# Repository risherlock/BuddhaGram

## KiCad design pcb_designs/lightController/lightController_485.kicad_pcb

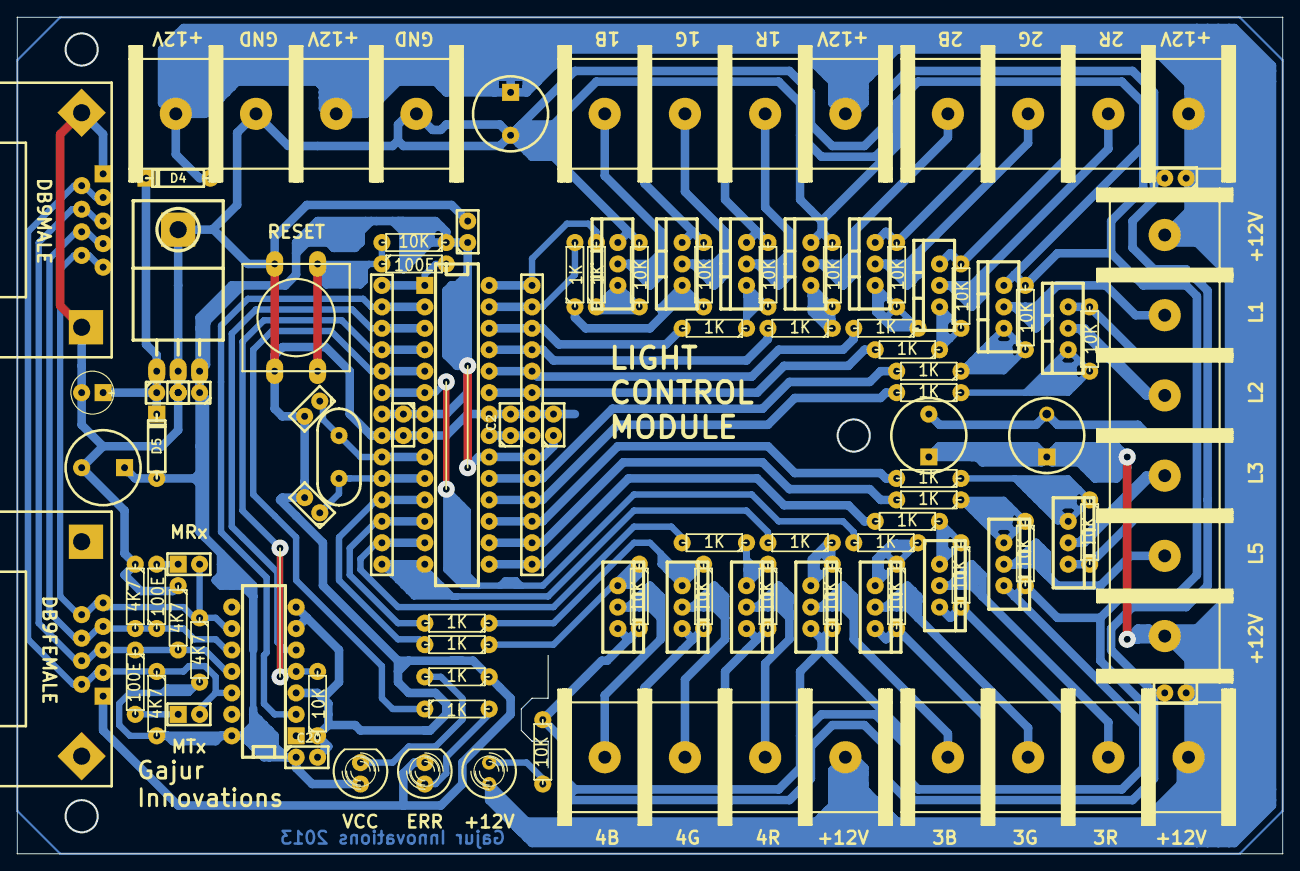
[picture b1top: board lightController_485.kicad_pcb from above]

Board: 2 copper layers, 149.9 x 99.1 mm, 98 parts (0 on the bottom side), 70 nets.

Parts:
C1, C3: 22pF; C1
C2, C5, C12, C13, C14, C15, C16, C20, C21: 104; C1
C4, C7, C8, C9: 1000uF; C2V8
C6: 1000uF; C1V5
D1, D2, D3: LED; LED-5MM
D4, D5: DIODE; D3
IC1: ATMEGA168-P; DIP-28__300
J1: DB9M; DB9MC
J2: DB9F; DB9FC
JP1, JP2: JUMPER; SIL-2
P1, P2: CONN_14; SIL-14
P3, P4, P5, P6, P7: CONN_4; CONN_4_SOLAR
P8: CONN_6; CONN_6_SOLAR
Q1, Q2, Q3, Q4, Q5, Q6, Q7, Q8, Q9, Q10, Q11, Q12, Q13, Q14, Q15, Q16: TIP122; TO-220_Neutral123_Vertical
R1, R4, R6, R7, R8, R9, R10, R11, R12, R13, R14, R15, R16, R17, R18, R19, R20, R21: 1K; R3
R2, R5, R22, R23, R24, R25, R26, R27, R28, R29, R30, R31, R32, R33, R34, R35, R36, R37, R38: 10K; R3
R3, R40, R43: 100E; R3
R39, R41, R42, R44: 4K7; R3
SW1: SW_PUSH; SW_PUSH-12mm
U1: 7805; TO-220_Neutral123_Horizontal
U2: MAX13080E; DIP-14__300
X1: 16MHz; HC-49V

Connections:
+12V: C7.1, C8.1, C9.1, C12.1, C13.1, D3.1, D4.1, P3.2, P3.4, P4.1, P5.1, P6.1, P7.1, P8.1, P8.6
/MISO: IC1.18, P2.4, R12.2
/MOSI: IC1.17, P2.3, R21.2
/P1: IC1.1, P1.1, R3.2
/P2: IC1.2, P1.2, U2.2
/P3: IC1.3, P1.3, U2.5
/P4: IC1.4, P1.4, R22.2, U2.4
/P5: IC1.5, P1.5, R1.1
/P6: IC1.6, P1.6, R18.2
/P9: C1.1, IC1.9, P1.9, X1.1
/P10: C3.1, IC1.10, P1.10, X1.2
/P11: IC1.11, P1.11, R16.2
/P12: IC1.12, P1.12, R15.2
/P13: IC1.13, P1.13, R14.2
/P14: IC1.14, P1.14, R19.2
/P15: IC1.15, P2.1, R17.2
/P16: IC1.16, P2.2, R20.2
/P19: IC1.19, P2.5, R13.2
/P21: C2.1, IC1.21, P2.7
/P23: IC1.23, P2.9, R9.2
/P24: IC1.24, P2.10, R10.2
/P25: IC1.25, P2.11, R11.2
/P26: IC1.26, P2.12, R6.2
/P27: IC1.27, P2.13, R7.2
/P28: IC1.28, P2.14, R8.2
/R0: J1.4, J1.8, J2.4, J2.8, R40.1, R41.2, U2.10
/R1: J1.5, J1.9, J2.5, J2.9, JP1.2, R39.1, U2.9
/RST_IN: R2.2, R3.1, SW1.2
/T0: J1.3, J1.7, J2.3, J2.7, R43.1, R44.2, U2.11
/T1: J1.2, J1.6, J2.2, J2.6, JP2.2, R42.1, U2.12
GND: C1.2, C2.2, C3.2, C4.2, C5.2, C6.2, C7.2, C8.2, C9.2, C12.2, C13.2, C14.2, C15.2, C16.2, C20.2, C21.2, D1.2, IC1.8, IC1.22, J1.1, J2.1, P1.8, P2.8, P3.1, P3.3, Q1.3, Q2.3, Q3.3, Q4.3, Q5.3, Q6.3, Q7.3, Q8.3, Q9.3, Q10.3, Q11.3, Q12.3, Q13.3, Q14.3, Q15.3, Q16.3, R4.1, R5.1, R22.1, R23.2, R24.2, R25.2, R26.2, R27.2, R28.2, R29.2, R30.2, R31.2, R32.2, R33.2, R34.2, R35.2, R36.2, R37.2, R38.2, R41.1, R44.1, SW1.1, U1.GND, U2.3, U2.6, U2.7
unnamed: P4.2, Q1.2
unnamed: D1.1, R1.2
unnamed: Q3.1, R8.1, R23.1
unnamed: Q2.1, R7.1, R24.1
unnamed: Q1.1, R6.1, R25.1
unnamed: Q6.1, R11.1, R26.1
unnamed: Q5.1, R10.1, R27.1
unnamed: Q4.1, R9.1, R28.1
unnamed: Q8.1, R13.1, R29.1
unnamed: Q7.1, R12.1, R30.1
unnamed: P8.2, Q15.2
unnamed: P8.4, Q7.2
unnamed: JP1.1, R40.2
unnamed: Q9.1, R14.1, R33.1
unnamed: Q11.1, R16.1, R31.1
unnamed: Q10.1, R15.1, R32.1
unnamed: Q14.1, R19.1, R34.1
unnamed: Q13.1, R18.1, R35.1
unnamed: Q12.1, R17.1, R36.1
unnamed: Q15.1, R20.1, R37.1
unnamed: Q16.1, R21.1, R38.1
unnamed: D3.2, R5.2
unnamed: D2.2, R4.2
unnamed: JP2.1, R43.2
unnamed: P6.2, Q9.2
unnamed: P4.4, Q3.2
unnamed: P4.3, Q2.2
unnamed: P5.2, Q4.2
unnamed: P5.4, Q6.2
unnamed: P5.3, Q5.2
unnamed: P6.4, Q11.2
unnamed: P6.3, Q10.2
unnamed: P7.2, Q12.2
unnamed: P7.4, Q14.2
unnamed: P7.3, Q13.2
unnamed: P8.3, Q16.2
unnamed: P8.5, Q8.2
unnamed: C6.1, C14.1, D4.2, D5.2, U1.VI
VCC: C4.1, C5.1, C15.1, C16.1, C20.1, C21.1, D2.1, D5.1, IC1.7, IC1.20, P1.7, P2.6, R2.1, R39.2, R42.2, U1.VO, U2.14

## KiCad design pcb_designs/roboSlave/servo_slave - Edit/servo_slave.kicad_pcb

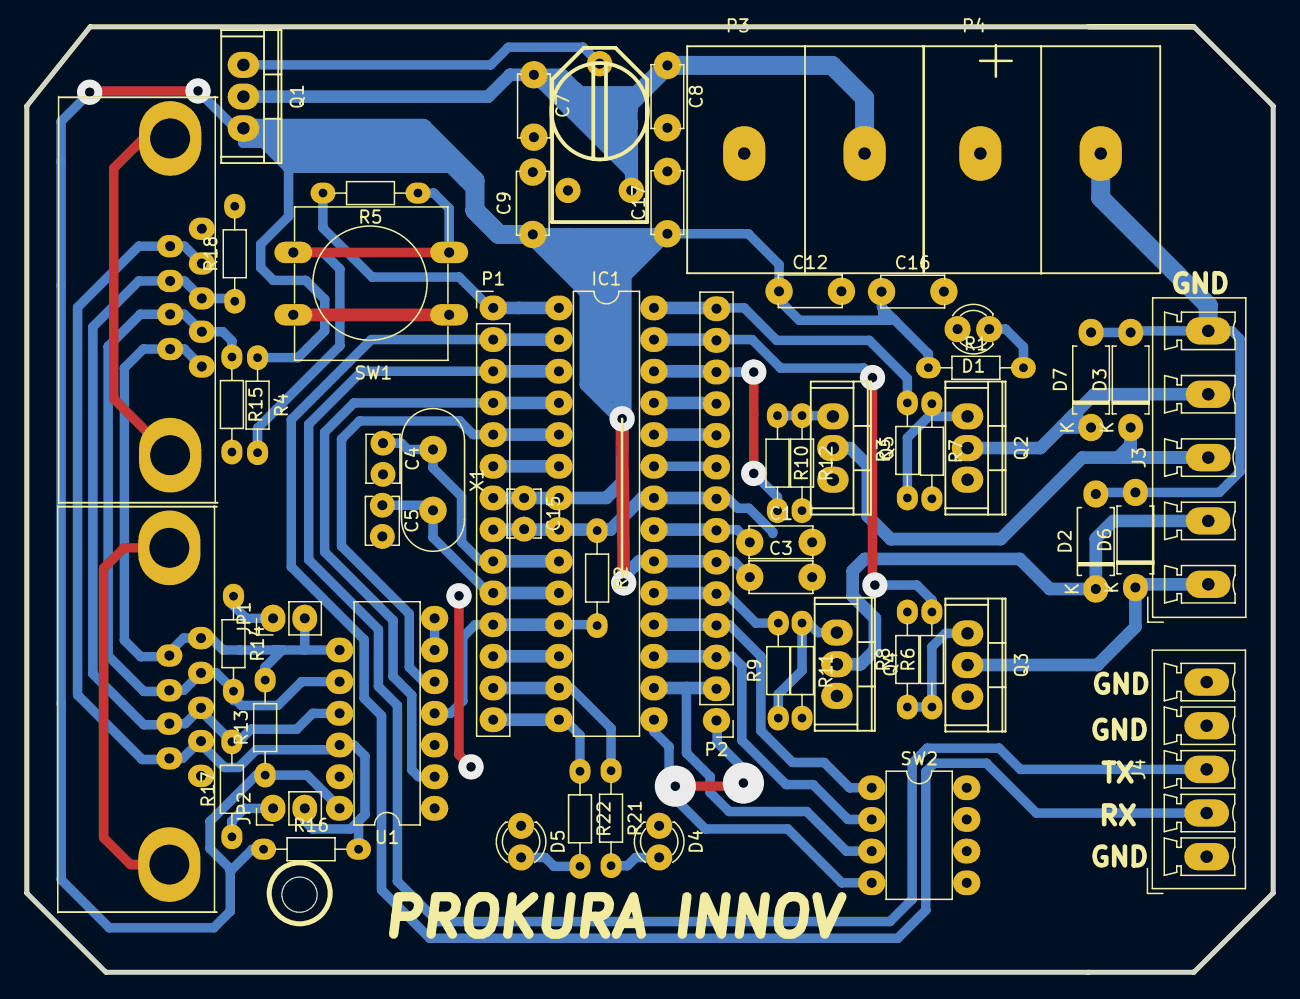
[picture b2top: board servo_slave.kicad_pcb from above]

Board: 2 copper layers, 99.9 x 75.8 mm, 59 parts (0 on the bottom side), 47 nets.

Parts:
C1, C3, C7, C8, C9, C12, C16, C17: 104; Ceramic_5.00
C4, C5: 22pF; Ceramic_2.54
C15: 104; Ceramic_2.54
D1, D4, D5: LED; Led_3mm
D2, D3, D6, D7: DIODE; Diode_1N4007
IC1: ATMEGA168-P; DIP-28_W7.62mm
J1: DB9_Female; DB9
J2: DB9_Male; DB9
J3: Conn_01x05_Male; PhoenixContact_MCV_1,5_5-G-5.08_1x05_P5.08mm_Vertical
J4: Conn_01x05_Male; PhoenixContact_MCV_1,5_5-G-3.5_1x05_P3.50mm_Vertical
JP1, JP2: Jumper; PinHeader_1x02_P2.54mm_Vertical
P1, P2: CONN_14; PinHeader_1x14_P2.54mm_Vertical
P3, P4: CONN_2; Solar_Connector0.1
Q1, Q2, Q3, Q4, Q5: TIP122; Voltage_Regulator
R1: 1K; R_Axial_DIN0204_L3.6mm_D1.6mm_P7.62mm_Horizontal
R2, R4: 10K; R_Axial_DIN0204_L3.6mm_D1.6mm_P7.62mm_Horizontal
R3, R6, R7, R8, R9, R10, R11, R12, R13, R14, R15, R16, R17, R18, R21, R22: R; R_Axial_DIN0204_L3.6mm_D1.6mm_P7.62mm_Horizontal
R5: 100E; R_Axial_DIN0204_L3.6mm_D1.6mm_P7.62mm_Horizontal
RV1: POT; Skeleton_Preset
SW1: SW_PUSH; SW_PUSH-12mm
SW2: Address; DIP-8_W7.62mm
U1: MAX13080E; DIP-14_W7.62mm
X1: 16MHz; Crystal_HC49-4H_Vertical

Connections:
+6V: C7.1, C8.1, P3.2, Q1.2, RV1.3
+12V: D2.2, D3.2, D6.2, D7.2, J3.5, P4.2
/25: D2.1, J3.2, Q4.2
/26: D3.1, J3.3, Q5.2
/27: D6.1, J3.1, Q3.2
/28: D7.1, J3.4, Q2.2
/A: J1.2, J1.6, J2.4, J2.9, JP2.2, R16.2, U1.12
/B: J1.3, J1.7, J2.3, J2.8, R17.2, R18.1, U1.11
/MISO: IC1.18, P2.4, SW2.1
/MOSI: IC1.17, P2.3, SW2.2
/P1: IC1.1, P1.1, R5.2
/P2: IC1.2, J4.2, P1.2
/P3: IC1.3, J4.3, P1.3
/P4: IC1.4, P1.4, U1.2
/P5: IC1.5, P1.5, U1.5
/P6: IC1.6, P1.6
/P9: C4.1, IC1.9, P1.9, X1.1
/P10: C5.1, IC1.10, P1.10, X1.2
/P11: IC1.11, P1.11, R2.2, U1.4
/P12: IC1.12, P1.12
/P13: IC1.13, P1.13, R21.1
/P14: IC1.14, P1.14, R22.1
/P15: IC1.15, P2.1, SW2.4
/P16: IC1.16, P2.2, SW2.3
/P19: IC1.19, P2.5, R9.2
/P21: C1.1, IC1.21, P2.7
/P23: IC1.23, P2.9
/P24: IC1.24, P2.10
/P25: IC1.25, P2.11
/P26: IC1.26, P2.12, R10.2
/P27: IC1.27, P2.13, R6.2
/P28: IC1.28, P2.14, R3.2
/RST_IN: R4.2, R5.1, SW1.2
/Y: J1.5, J1.9, J2.1, J2.6, JP1.2, R13.2, U1.9
/Z: J1.4, J1.8, J2.2, J2.7, R14.2, R15.1, U1.10
GND: C1.2, C3.2, C4.2, C5.2, C7.2, C8.2, C9.2, C12.2, C15.2, C16.2, C17.2, D1.2, D4.1, D5.1, IC1.8, IC1.22, J1.1, J2.5, J4.1, J4.4, J4.5, P1.8, P2.8, P3.1, P4.1, Q2.3, Q3.3, Q4.3, Q5.3, R2.1, R7.2, R8.2, R11.2, R12.2, R15.2, R18.2, RV1.1, SW1.1, SW2.5, SW2.6, SW2.7, SW2.8, U1.3, U1.6, U1.7
unnamed: D1.1, R1.2
unnamed: D4.2, R21.2
unnamed: D5.2, R22.2
unnamed: JP1.1, R14.1
unnamed: JP2.1, R17.1
unnamed: Q1.1, RV1.2
unnamed: Q2.1, R3.1, R7.1
unnamed: Q3.1, R6.1, R8.1
unnamed: Q4.1, R9.1, R11.1
unnamed: Q5.1, R10.1, R12.1
VCC: C3.1, C9.1, C12.1, C15.1, C16.1, C17.1, IC1.7, IC1.20, P1.7, P2.6, Q1.3, R1.1, R4.1, R13.1, R16.1, U1.14

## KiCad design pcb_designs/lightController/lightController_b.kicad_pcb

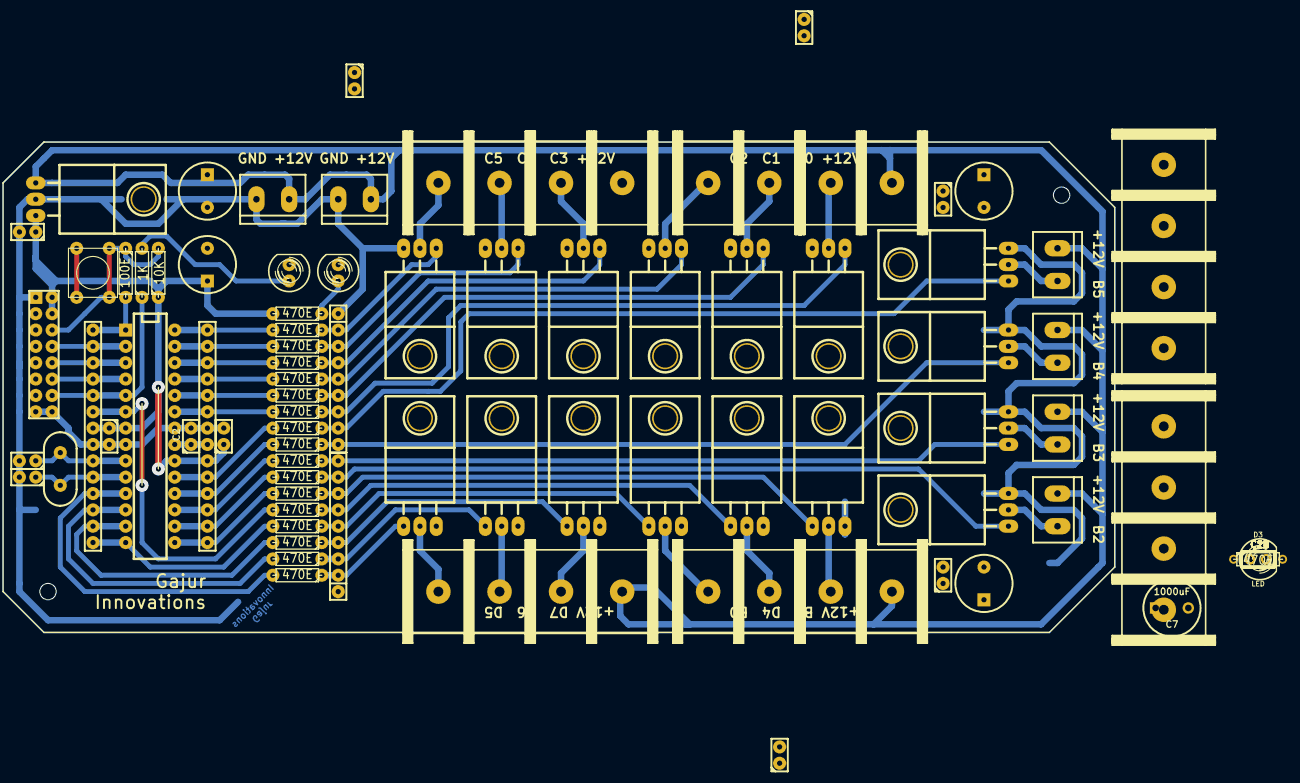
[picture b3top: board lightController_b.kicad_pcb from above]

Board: 2 copper layers, 89 parts (0 on the bottom side), 63 nets.

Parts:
C1, C3: 22pF; C1
C2, C5, C10, C11, C12, C13, C14, C15, C16, C17, C18, C19, C20, C21, C22, C23, C24: 104; C1
C4, C6, C7, C8, C9: 1000uF; C2V8
D1, D2, D3: LED; LED-5MM
IC1: ATMEGA168-P; DIP-28__300
P1, P2: CONN_14; SIL-14
P1#2, P1#3: CONN_4; CONN_4_SOLAR
P3, P4, P10, P11, P16, P17: CONN_2; bornier2
P5: CONN_8X2; pin_array_8x2
P6, P7, P8, P9, P12, P13, P14, P15: CONN_2; CONN_2_SOLAR
Q1, Q2, Q3, Q4, Q5, Q6, Q7, Q8, Q9, Q10, Q11, Q12, Q13, Q14, Q15, Q16: TIP122; TO-220_Neutral123_Horizontal
R1: 1K; R3
R2: 10K; R3
R3: 100E; R3
R4, R5, R6, R7, R8, R9, R10, R11, R12, R13, R14, R15, R16, R17, R18, R19, R20, R21: 470E; R3
RR1, RR2: RR8; r_pack8
SW1: SW_PUSH; SW_PUSH_SMALL
U1: 7805; TO-220_Neutral123_Horizontal
X1: 16MHz; HC-49V

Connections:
+12V: C6.1, C7.1, C8.1, C9.1, C10.1, C11.1, C12.1, C13.1, C14.1, P3.2, P4.2, P6.1, P8.1, P10.2, P11.2, P12.1, P14.1, P16.2, P17.2, R5.2, U1.VI
/MISO: IC1.18, P2.4, R12.2
/MOSI: IC1.17, P2.3, R21.2
/P1: IC1.1, P1.1, R3.2
/P2: IC1.2, P1.2, P5.8
/P3: IC1.3, P1.3, P5.10
/P4: IC1.4, P1.4, P5.12
/P5: IC1.5, P1.5, P5.14, R1.1
/P6: IC1.6, P1.6, R18.2
/P9: C1.1, IC1.9, P1.9, X1.1
/P10: C3.1, IC1.10, P1.10, X1.2
/P11: IC1.11, P1.11, R16.2
/P12: IC1.12, P1.12, R15.2
/P13: IC1.13, P1.13, R14.2
/P14: IC1.14, P1.14, R19.2
/P15: IC1.15, P2.1, R17.2
/P16: IC1.16, P2.2, R20.2
/P19: IC1.19, P2.5, R13.2
/P21: C2.1, IC1.21, P2.7
/P23: IC1.23, P2.9, R9.2
/P24: IC1.24, P2.10, R10.2
/P25: IC1.25, P2.11, R11.2
/P26: IC1.26, P2.12, R6.2
/P27: IC1.27, P2.13, R7.2
/P28: IC1.28, P2.14, R8.2
/RST_IN: P5.6, R2.2, R3.1, SW1.2
GND: C1.2, C2.2, C3.2, C4.2, C5.2, C6.2, C7.2, C8.2, C9.2, C10.2, C11.2, C12.2, C13.2, C14.2, C15.2, C16.2, C17.2, C18.2, C19.2, C20.2, C21.2, C22.2, C23.2, C24.2, D1.2, D2.2, D3.2, IC1.8, IC1.22, P1.8, P2.8, P3.1, P4.1, P5.1, P5.3, P5.5, P5.7, P5.9, P5.11, P5.13, P5.15, P5.16, Q1.3, Q2.3, Q3.3, Q4.3, Q5.3, Q6.3, Q7.3, Q8.3, Q9.3, Q10.3, Q11.3, Q12.3, Q13.3, Q14.3, Q15.3, Q16.3, RR1.1, RR2.1, SW1.1, U1.GND
unnamed: P6.2, Q1.2
unnamed: P7.1, Q2.2
unnamed: P7.2, Q3.2
unnamed: P10.1, Q7.2
unnamed: P8.2, Q4.2
unnamed: P11.1, Q8.2
unnamed: P9.1, Q5.2
unnamed: P9.2, Q6.2
unnamed: D2.1, R4.1
unnamed: D3.1, R5.1
unnamed: D1.1, R1.2
unnamed: P15.1, Q13.2
unnamed: P14.2, Q12.2
unnamed: P17.1, Q16.2
unnamed: P15.2, Q14.2
unnamed: Q14.1, R19.1, RR2.5
unnamed: Q8.1, R13.1, RR1.8
unnamed: Q7.1, R12.1, RR1.9
unnamed: Q4.1, R9.1, RR1.7
unnamed: Q13.1, R18.1, RR2.6
unnamed: Q12.1, R17.1, RR2.7
unnamed: Q16.1, R21.1, RR2.9
unnamed: Q3.1, R8.1, RR1.2
unnamed: Q2.1, R7.1, RR1.3
unnamed: Q1.1, R6.1, RR1.4
unnamed: Q6.1, R11.1, RR1.5
unnamed: Q5.1, R10.1, RR1.6
unnamed: Q10.1, R15.1, RR2.3
unnamed: Q11.1, R16.1, RR2.2
unnamed: P16.1, Q15.2
unnamed: Q15.1, R20.1, RR2.8
unnamed: Q9.1, R14.1, RR2.4
unnamed: P13.1, Q10.2
unnamed: P12.2, Q9.2
unnamed: P13.2, Q11.2
VCC: C4.1, C5.1, C15.1, C16.1, C17.1, C18.1, C19.1, C20.1, C21.1, C22.1, C23.1, C24.1, IC1.7, IC1.20, P1.7, P2.6, P5.2, P5.4, R2.1, R4.2, U1.VO

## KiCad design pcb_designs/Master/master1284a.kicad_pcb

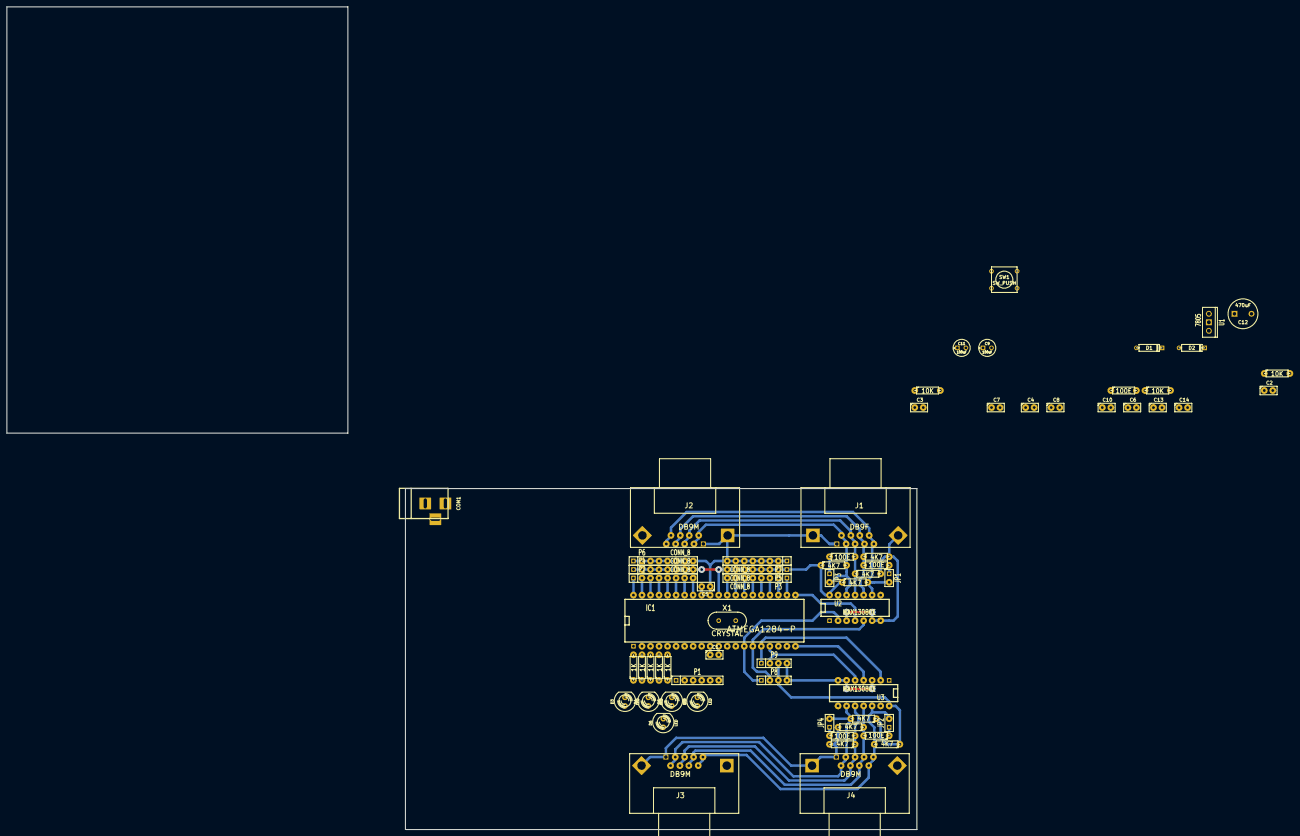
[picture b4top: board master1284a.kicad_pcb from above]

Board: 2 copper layers, 271.1 x 245.1 mm, 66 parts (0 on the bottom side), 56 nets.

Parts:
C1, C3, C4, C5, C6, C8, C10, C14: 104; C1
C2, C7: 22pF; C1
C9, C11: 100uF; C1V5
C12: 470uF; C2V8
C13: 100uF; C1
CON1: BARREL_JACK
D1, D2: DIODE; D3
D3, D4, D5, D6, D7: LED; LED-5MM
IC1: ATMEGA1284-P; DIP-40__600
J1: DB9F; DB9FC
J2, J3, J4: DB9M; DB9MC
JP1, JP2, JP3, JP4: JUMPER; SIL-2
P1: CONN_6; SIL-6
P2, P3, P4, P5, P6, P7: CONN_8; SIL-8
P8, P9: CONN_4; SIL-4
R1, R11, R14, R17, R20: 100E; R3
R2, R8, R9: 10K; R3
R3, R4, R5, R6, R7: 1K; R3
R10, R12, R13, R15, R16, R18, R19, R21: 4K7; R3
SW1: SW_PUSH; SW_PUSH_SMALL
U1: 7805; LM78XXV
U2, U3: MAX13080E; DIP-14__300
X1: CRYSTAL; HC-49V

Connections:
/MISO: IC1.7, P1.4
/MOSI: IC1.6, P1.6
/R0_M: J1.4, J1.8, J2.4, J2.8, R11.2, R12.1, U2.10
/R0_S: J3.4, J3.8, J4.4, J4.8, R14.2, R15.1, U3.11
/R1_M: J1.5, J1.9, J2.5, J2.9, JP1.2, R10.2, U2.9
/R1_S: J3.5, J3.9, J4.5, J4.9, JP2.2, R13.2, U3.12
/RST: IC1.9, P1.1, R1.1, R2.2
/RTS_M: IC1.21, R8.2, U2.4
/RTS_S: IC1.20, R9.2, U3.4
/RX_M: IC1.14, P8.1, U2.2
/RX_S: IC1.16, P9.1, U3.2
/SCK: IC1.8, P1.5
/T0_M: J1.3, J1.7, J2.3, J2.7, R17.2, R18.1, U2.11
/T0_S: J3.3, J3.7, J4.3, J4.7, R20.2, R21.1, U3.10
/T1_M: J1.2, J1.6, J2.2, J2.6, JP3.2, R16.2, U2.12
/T1_S: J3.2, J3.6, J4.2, J4.6, JP4.2, R19.2, U3.9
/TX_M: IC1.15, P8.2, U2.5
/TX_S: IC1.17, P9.2, U3.5
GND: C1.2, C2.2, C3.2, C4.2, C5.1, C6.2, C7.2, C8.2, C9.2, C10.2, C11.2, C12.2, C13.2, C14.2, CON1.2, IC1.11, IC1.31, J1.1, J2.1, J3.1, J4.1, P1.3, P6.1, P6.2, P6.3, P6.4, P6.5, P6.6, P6.7, P6.8, P7.1, P7.2, P7.3, P7.4, P7.5, P7.6, P7.7, P7.8, P8.4, P9.4, R8.1, R9.1, R12.2, R15.2, R18.2, R21.2, SW1.1, U1.GND, U2.3, U2.6, U2.7, U3.3, U3.6, U3.7
unnamed: IC1.33, P2.8
unnamed: IC1.26, P3.5
unnamed: IC1.27, P3.6
unnamed: IC1.28, P3.7
unnamed: IC1.29, P3.8
unnamed: IC1.25, P3.4
unnamed: IC1.23, P3.2
unnamed: IC1.5, R7.2
unnamed: IC1.4, R6.2
unnamed: IC1.22, P3.1
unnamed: IC1.34, P2.7
unnamed: IC1.24, P3.3
unnamed: CON1.1, D1.1
unnamed: IC1.36, P2.5
unnamed: IC1.40, P2.1
unnamed: IC1.39, P2.2
unnamed: IC1.38, P2.3
unnamed: IC1.37, P2.4
unnamed: IC1.35, P2.6
unnamed: IC1.3, R5.2
unnamed: D4.2, R4.1
unnamed: IC1.2, R4.2
unnamed: D3.2, R3.1
unnamed: IC1.1, R3.2
unnamed: D6.2, R6.1
unnamed: D5.2, R5.1
unnamed: D7.2, R7.1
unnamed: R1.2, SW1.2
unnamed: C5.2, IC1.32
unnamed: C7.1, IC1.13, X1.2
unnamed: C2.1, IC1.12, X1.1
unnamed: JP3.1, R17.1
unnamed: JP2.1, R14.1
unnamed: JP1.1, R11.1
unnamed: C10.1, C12.1, D1.2, D2.2, U1.VI
unnamed: JP4.1, R20.1
VCC: C1.1, C3.1, C4.1, C6.1, C8.1, C9.1, C11.1, C13.1, C14.1, D2.1, D3.1, D4.1, D5.1, D6.1, D7.1, IC1.10, IC1.30, P1.2, P4.1, P4.2, P4.3, P4.4, P4.5, P4.6, P4.7, P4.8, P5.1, P5.2, P5.3, P5.4, P5.5, P5.6, P5.7, P5.8, P8.3, P9.3, R2.1, R10.1, R13.1, R16.1, R19.1, U1.VO, U2.14, U3.14

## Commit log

2020-04-29 Add Master files via upload
2020-04-29 Add DMX controller files
2020-04-29 Add irSlave board files
2020-04-29 Add robot actuation controller files
2020-04-29 Add lightController files
2020-04-29 Add reference documents via upload
2021-11-01 Add PCB design files
2022-10-16 Add the firmware with MP3 module
2022-10-16 Remove temp files
